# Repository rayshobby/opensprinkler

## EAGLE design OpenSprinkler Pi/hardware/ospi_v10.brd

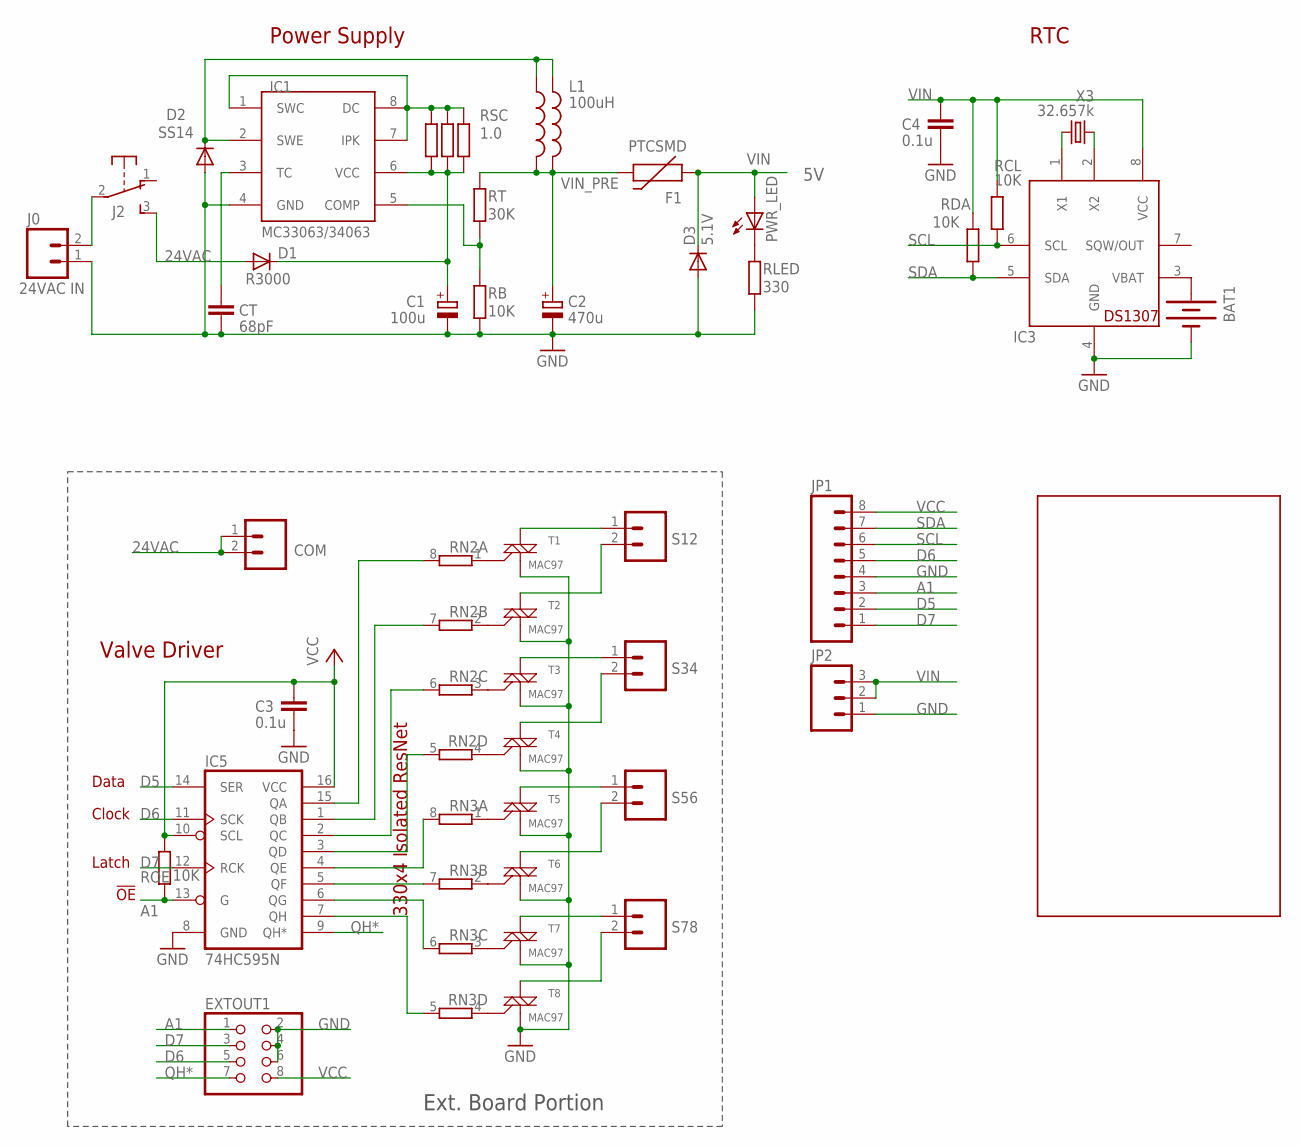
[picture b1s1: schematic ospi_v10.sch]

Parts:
BAT1: BATTERYBATTERY_12MM_SMT; BATTCON_12MM_SMT
C1: 100u; E3,5-8
C2: 470u; E3,5-8
C3, C4: 0.1u; C0805
COM: M025MM; SCREWTERMINAL-5MM-2
CT: 68pF; C0805
D1: R3000; DO41-7.6
D2: SS14; DO-214AC
D3: 5.1V; DO34-7
EXTOUT1: PINHD-2X4/90; 2X04/90
F1: PTCSMD; PTC-1206
IC1: MC33063/MC34063D; SO08
IC3: DS1307; SO08
IC5: 74HC595N; SO16
J0: 24VAC IN; SCREWTERMINAL-5MM-2
J2: EG1206
JP1: M08LOCK; 1X08_LOCK
JP2: M03LOCK; 1X03_LOCK
L1: 100uH; SRU1038
L1': 220uH; 6000-XXXX-RC
PWR_LED: LEDCHIPLED_0805; CHIPLED_0805
RB: 10K; R0805
RCL: 10K; R0805
RDA: 10K; R0805
RLED: 330; R0805
RN2, RN3: 4R-NEXB38V; EXB38V
ROE: 10K; R0805
RSC, RSC1, RSC2: 1.0; R0805
RT: 30K; R0805
S12, S34, S56, S78: M025MM; SCREWTERMINAL-5MM-2
T1, T2, T3, T4, T5, T6, T7, T8: MAC97; SOT223
U$2: OSPI
X3: 32.657k; TC26H

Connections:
24VAC: COM.1, COM.2, D1.A, J2.3 (S)
A1: EXTOUT1.1, IC5.13 (G), JP1.3, ROE.1
D5: IC5.14 (SER), JP1.2
D6: EXTOUT1.5, IC5.11 (SCK), JP1.5
D7: EXTOUT1.3, IC5.12 (RCK), JP1.1
GND: BAT1.P$1 (-), C1.-, C2.-, C3.2, C4.2, CT.2, D2.A, D3.A, EXTOUT1.2, EXTOUT1.4, EXTOUT1.6, IC1.4 (GND), IC3.4 (GND), IC5.8 (GND), J0.1, JP1.4, JP2.1, RB.2, RLED.2, T1.1 (M1), T2.1 (M1), T3.1 (M1), T4.1 (M1), T5.1 (M1), T6.1 (M1), T7.1 (M1), T8.1 (M1)
unnamed: PWR_LED.C, RLED.1
unnamed: C1.+, D1.C, IC1.6 (VCC), RSC.2, RSC1.2, RSC2.2
unnamed: RN2.1, T1.3 (G)
unnamed: IC5.5 (QF), RN3.7 (2)
unnamed: IC5.6 (QG), RN3.6 (2)
unnamed: J0.2, J2.2
unnamed: IC5.7 (QH), RN3.5 (2)
unnamed: IC5.4 (QE), RN3.8 (2)
unnamed: IC5.3 (QD), RN2.5 (2)
unnamed: IC5.2 (QC), RN2.6 (2)
unnamed: IC5.1 (QB), RN2.7 (2)
unnamed: IC5.15 (QA), RN2.8 (2)
unnamed: RN2.2 (1), T2.3 (G)
unnamed: S12.1, T1.4 (M2)
unnamed: S12.2, T2.4 (M2)
unnamed: S34.1, T3.4 (M2)
unnamed: RN2.3 (1), T3.3 (G)
unnamed: S34.2, T4.4 (M2)
unnamed: RN2.4 (1), T4.3 (G)
unnamed: S56.1, T5.4 (M2)
unnamed: S56.2, T6.4 (M2)
unnamed: S78.1, T7.4 (M2)
unnamed: S78.2, T8.4 (M2)
unnamed: RN3.1, T5.3 (G)
unnamed: RN3.2 (1), T6.3 (G)
unnamed: RN3.3 (1), T7.3 (G)
unnamed: RN3.4 (1), T8.3 (G)
unnamed: BAT1.P$2 (+), IC3.3 (VBAT)
unnamed: IC1.1 (SWC), IC1.7 (IPK), IC1.8 (DC), RSC.1, RSC1.1, RSC2.1
unnamed: D2.C, IC1.2 (SWE), L1.1, L1'.1
unnamed: IC3.1 (X1), X3.1
unnamed: CT.1, IC1.3 (TC)
unnamed: IC3.2 (X2), X3.2
unnamed: IC1.5 (COMP), RB.1, RT.2
QH*: EXTOUT1.7, IC5.9 (QH*)
SCL: IC3.6 (SCL), JP1.6, RCL.2
SDA: IC3.5 (SDA), JP1.7, RDA.2
VCC: C3.1, EXTOUT1.8, IC5.10 (SCL), IC5.16 (VCC), JP1.8, ROE.2
VIN: C4.1, D3.C, F1.1, IC3.8 (VCC), JP2.2, JP2.3, PWR_LED.A, RCL.1, RDA.1
VIN_PRE: C2.+, F1.2, L1.2, L1'.2, RT.1

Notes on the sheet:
Power Supply
Valve Driver
Data
Clock
Latch
330x4 Isolated ResNet
Ext. Board Portion
!OE
RTC

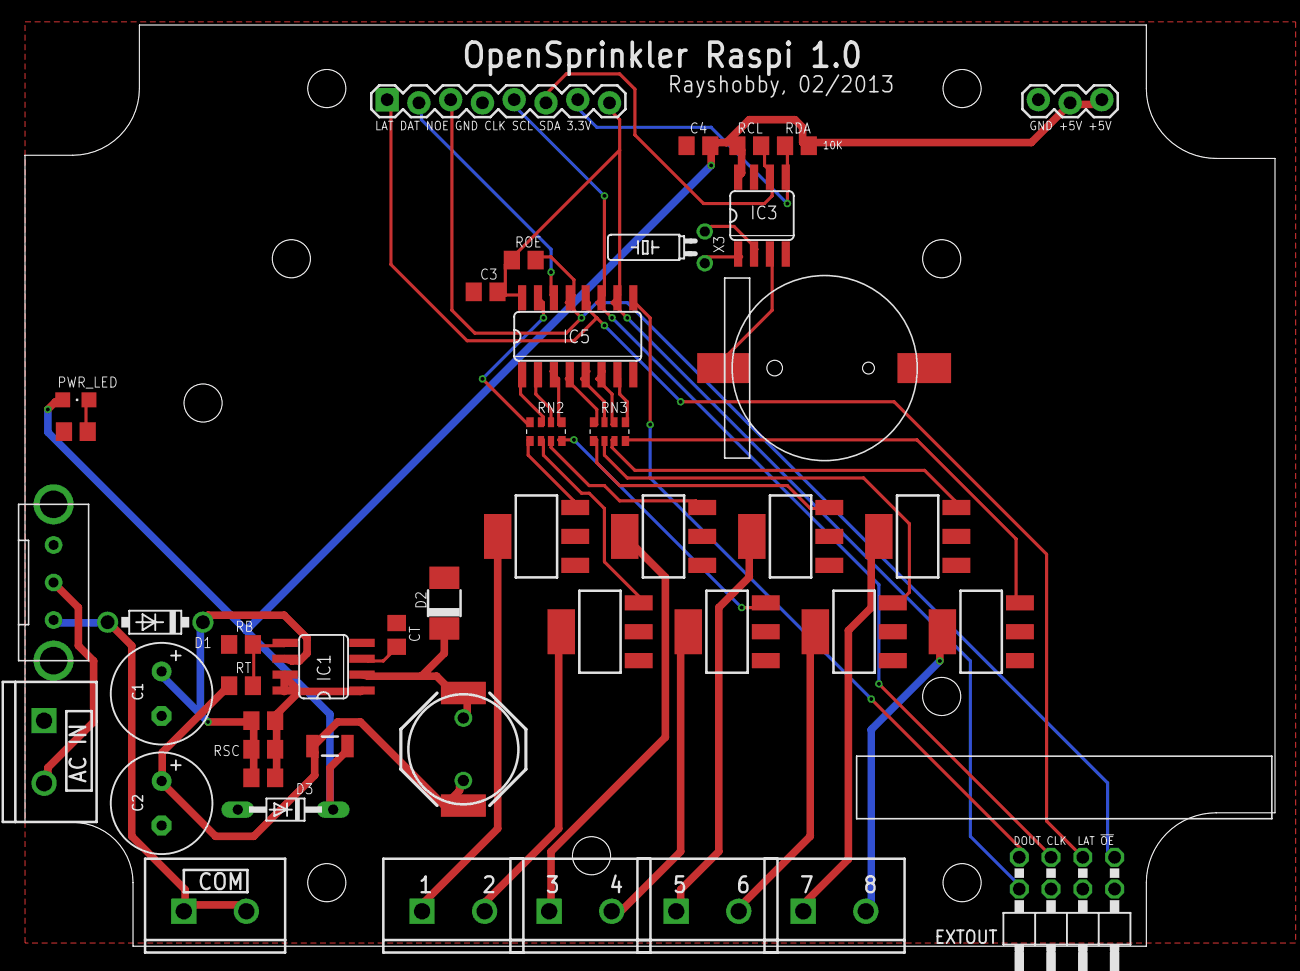
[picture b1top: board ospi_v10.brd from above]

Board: 2 copper layers, 99.9 x 73.7 mm, 47 parts (0 on the bottom side), 46 nets.

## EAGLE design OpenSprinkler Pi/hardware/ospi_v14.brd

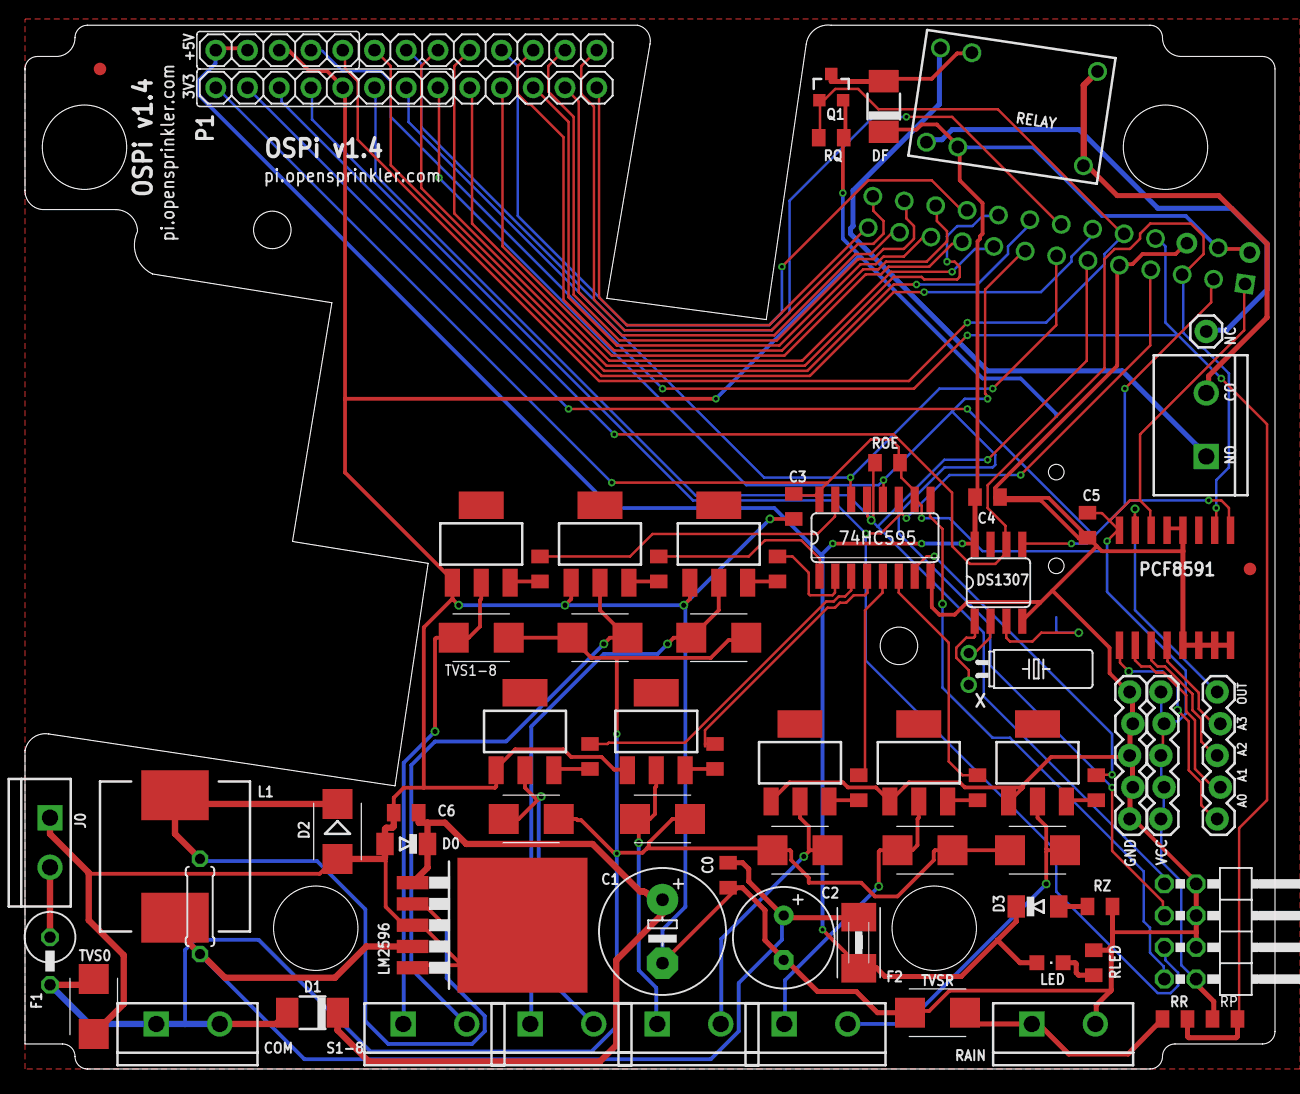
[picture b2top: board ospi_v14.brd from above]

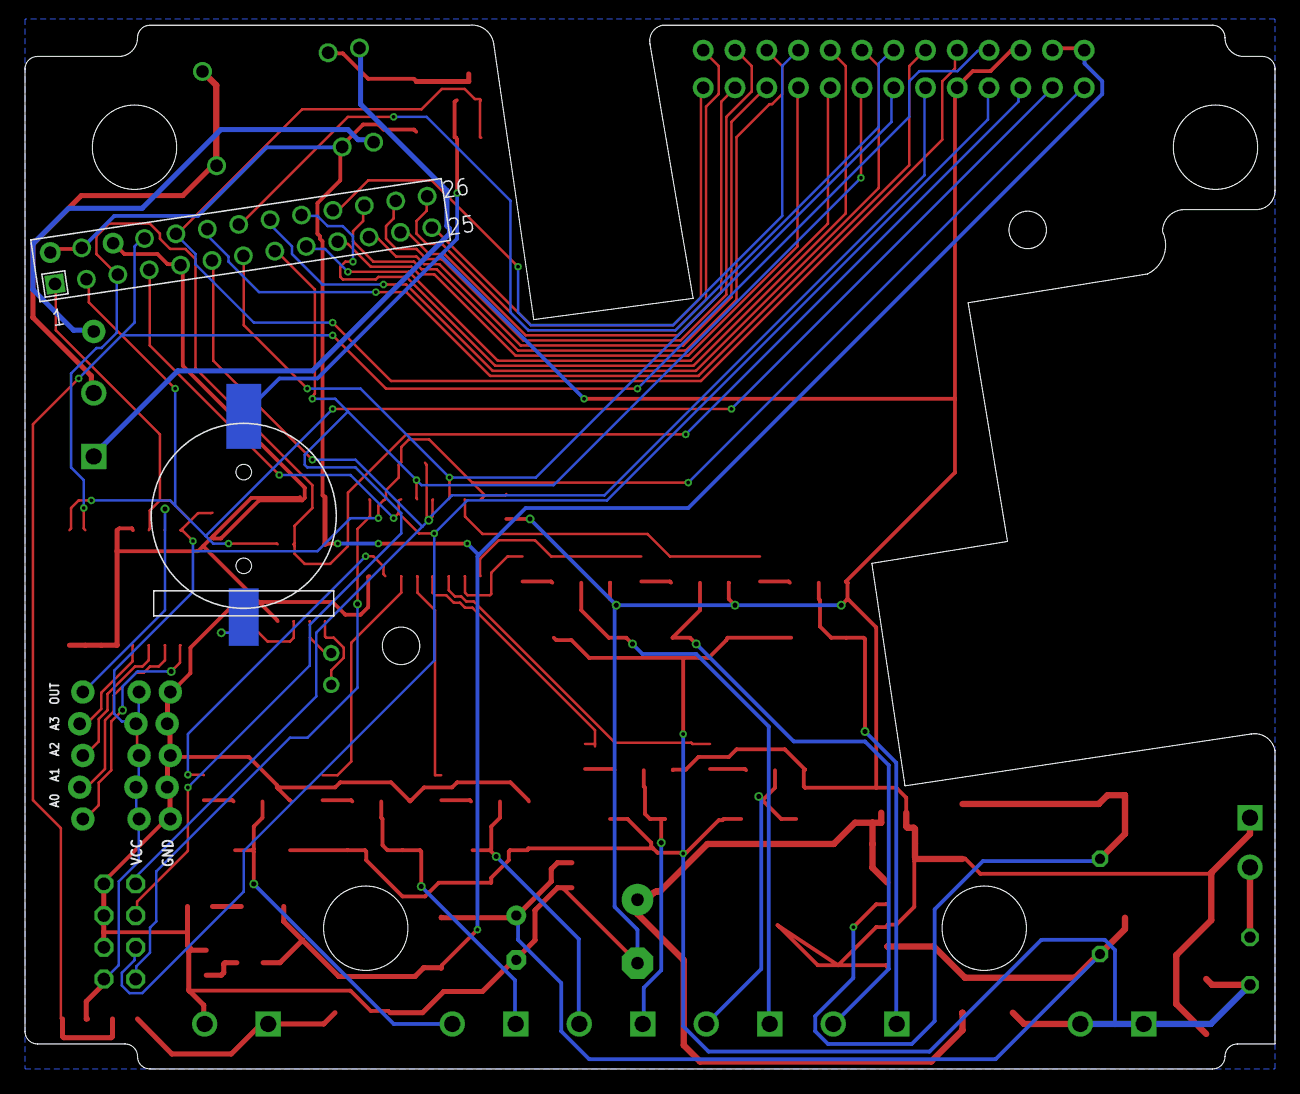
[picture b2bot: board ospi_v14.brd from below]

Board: 2 copper layers, 100.0 x 83.5 mm, 75 parts (2 on the bottom side), 69 nets.

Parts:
74HC595: 74HC595N; SO16
BAT: BATTCON_12MM_SMT
C0, C3, C4, C5, C6: 0.1u; C0805K
C1: 220uF/63V; E5-10,5
C2: 100u; E3,5-8
COM: SCREWTERMINAL-5MM-2-X
D0: 43V; MINIMELF
D1: S1B; DO-214AC
D2: SS24; SMB
D3: 5.6V; MINIMELF
DF: S1B; DO-214AC
DS1307: DS1307; SO08
EXTOUT1: 2X04/90
F1: 2A; 0411V
F2: 1812
J0: 24VAC IN; SCREWTERMINAL-4MM-2-X
JP1: M01PTH; 1X01
JP2, JP3: 1X13-BIG
JP5, JP6, JP7: 1X05_LOCK
L1: 150uH; CDRH125
L1': 150uH; 0207/7
LED: CHIPLED_0805
LM2596: TO263-5
PCF8591: PCF8591T; SO16W
Q1: 2N7002; SOT23-3
R1, R2, R4, R5, R6, R7, R8: 220; R0805
R3: 220\; R0805
RAIN: SCREWTERMINAL-5MM-2-X
RELAY: RELAY-2; RELAY-HK4100F
RLED: 1K; R0805
RLPORT: SCREWTERMINAL-5MM-2
ROE: 10K; R0805
RP: 30K; R0805
RQ: 10K; R0805
RR: 4.7K; R0805
RZ: 10; R0805
S12, S34, S56, S78: SCREWTERMINAL-5MM-2-X
T1, T2, T3, T4, T5, T6, T7, T8: MAC97; SOT223
TVS0, TVS1, TVS2, TVS3, TVS4, TVS5, TVS6, TVS7, TVS8: TVSSMB; SMB
TVSR: TVSSMB; SMB
U$1, U$3: FIDUCIAL; FIDUCIAL_1MM
U$2: RASPBERRY-PI
X: 32.768kHz; TC38H

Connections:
24VAC: COM.1, COM.2, D1.A, F1.2, TVS0.C, TVS1.C, TVS2.C, TVS3.C, TVS4.C, TVS5.C, TVS6.C, TVS7.C, TVS8.C
A1: 74HC595.13, EXTOUT1.1, JP2.8, ROE.1, U$2.11
ACIN: F1.1, J0.2
AIN0: JP5.1, PCF8591.1
AIN1: JP5.2, PCF8591.2
AIN2: JP5.3, PCF8591.3
AIN3: JP5.4, PCF8591.4
AOUT: JP5.5, PCF8591.15
CO: RELAY.5, RELAY.6, RLPORT.2
D5: 74HC595.14, JP2.7, U$2.13
D6: 74HC595.11, EXTOUT1.5, JP2.10, U$2.7
D7: 74HC595.12, EXTOUT1.3, JP2.6, U$2.15
GND: 74HC595.8, BAT.P$1, C0.2, C1.-, C2.-, C3.2, C4.2, C5.2, C6.2, D0.A, D2.A, DS1307.4, EXTOUT1.2, EXTOUT1.4, EXTOUT1.6, J0.1, JP2.9, JP3.11, JP7.1, JP7.2, JP7.3, JP7.4, JP7.5, LM2596.3, LM2596.5, LM2596.6, PCF8591.5, PCF8591.6, PCF8591.7, PCF8591.8, PCF8591.12, PCF8591.13, Q1.2, RAIN.2, RLED.2, RQ.2, RZ.2, T1.1, T2.1, T3.1, T4.1, T5.1, T6.1, T7.1, T8.1, TVS0.A, TVSR.A, U$2.6, U$2.9
unnamed: LED.C, RLED.1
unnamed: C1.+, C6.1, D0.C, D1.C, LM2596.1
unnamed: R1.2, T1.3
unnamed: 74HC595.5, R6.1
unnamed: 74HC595.6, R7.1
unnamed: D3.A, RZ.1
unnamed: 74HC595.7, R8.1
unnamed: D2.C, L1.1, L1'.1, LM2596.2
unnamed: DS1307.1, X.2
unnamed: 74HC595.4, R5.1
unnamed: 74HC595.3, R4.1
unnamed: 74HC595.2, R3.1
unnamed: 74HC595.1, R2.1
unnamed: 74HC595.15, R1.1
unnamed: R2.2, T2.3
unnamed: S12.1, T1.2, TVS1.A
unnamed: S12.2, T2.2, TVS2.A
unnamed: S34.1, T3.2, TVS3.A
unnamed: R3.2, T3.3
unnamed: S34.2, T4.2, TVS4.A
unnamed: R4.2, T4.3
unnamed: S56.1, T5.2, TVS5.A
unnamed: S56.2, T6.2, TVS6.A
unnamed: S78.1, T7.2, TVS7.A
unnamed: S78.2, T8.2, TVS8.A
unnamed: R5.2, T5.3
unnamed: R6.2, T6.3
unnamed: R7.2, T7.3
unnamed: R8.2, T8.3
unnamed: DS1307.2, X.1
unnamed: RAIN.1, RR.1, TVSR.C
unnamed: BAT.P$2, DS1307.3
unnamed: JP3.8, U$2.12
unnamed: JP3.7, U$2.14
unnamed: JP3.6, U$2.16
unnamed: JP2.5, U$2.17
unnamed: JP2.4, U$2.19
unnamed: JP2.3, U$2.21
unnamed: JP2.2, U$2.23
unnamed: JP2.1, U$2.25
unnamed: JP3.5, U$2.18
unnamed: JP3.4, U$2.20
unnamed: JP3.3, U$2.22
unnamed: JP3.2, U$2.24
unnamed: JP3.1, U$2.26
unnamed: DF.A, Q1.3, RELAY.9
NC: JP1.1, RELAY.1
NO: RELAY.10, RLPORT.1
QH*: 74HC595.9, EXTOUT1.7
RL: JP3.9, Q1.1, RQ.1, U$2.10
RS: JP3.10, RP.1, RR.2, U$2.8
SCL: DS1307.6, JP2.11, PCF8591.10, U$2.5
SDA: DS1307.5, JP2.12, PCF8591.9, U$2.3
VCC: 74HC595.10, 74HC595.16, C3.1, C5.1, EXTOUT1.8, JP2.13, JP6.1, JP6.2, JP6.3, JP6.4, JP6.5, PCF8591.14, PCF8591.16, ROE.2, RP.2, U$2.1
VIN: C4.1, D3.C, DF.C, DS1307.8, F2.2, JP3.12, JP3.13, LED.A, RELAY.2, U$2.2, U$2.4
VIN_PRE: C0.1, C2.+, F2.1, L1.2, L1'.2, LM2596.4
